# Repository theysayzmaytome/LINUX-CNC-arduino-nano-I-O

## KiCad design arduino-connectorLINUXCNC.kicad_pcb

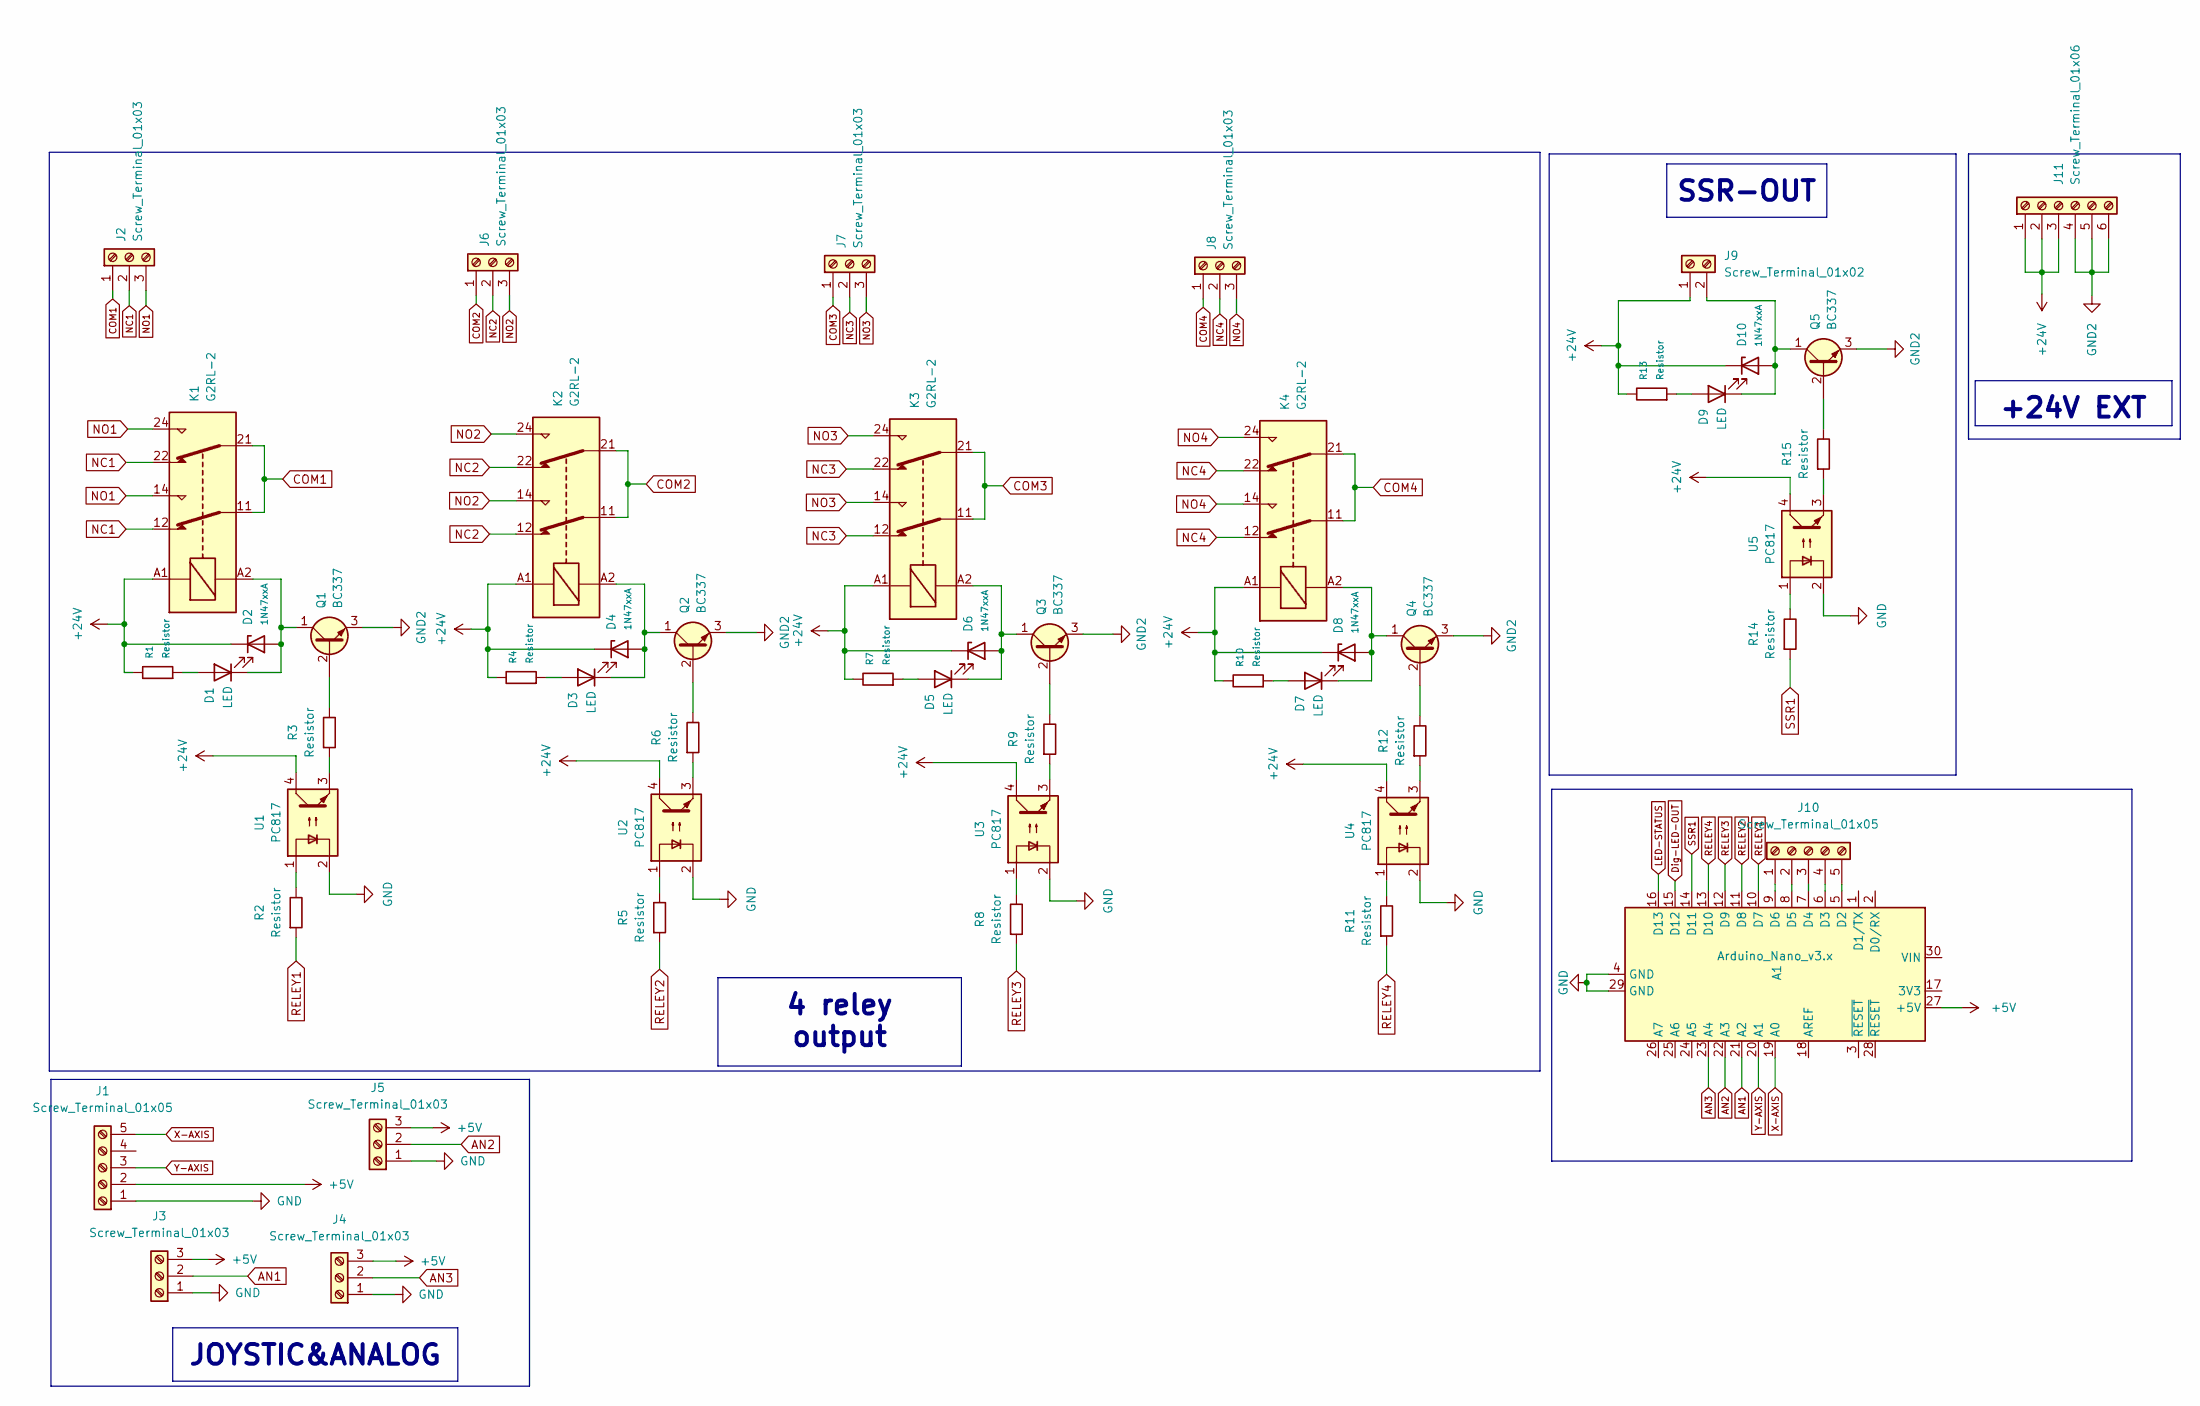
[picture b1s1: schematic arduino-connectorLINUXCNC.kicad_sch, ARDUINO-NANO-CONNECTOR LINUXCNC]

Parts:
A1: Arduino_Nano_v3.x; Arduino_Nano
D1, D3, D5, D7, D9: LED; LED_D5.0mm
D2, D4, D6, D8, D10: 1N47xxA; D_DO-41_SOD81_P10.16mm_Horizontal
J1, J10: Screw_Terminal_01x05; TerminalBlock_MetzConnect_Type011_RT05505HBWC_1x05_P5.00mm_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
J2, J3, J4, J5, J6, J7, J8: Screw_Terminal_01x03; TerminalBlock_Phoenix_MKDS-1,5-3_1x03_P5.00mm_Horizontal
J9: Screw_Terminal_01x02; TerminalBlock_Phoenix_MKDS-1,5-2-5.08_1x02_P5.08mm_Horizont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
J11: Screw_Terminal_01x06; TerminalBlock_Phoenix_MKDS-1,5-6_1x06_P5.00mm_Horizontal
K1, K2, K3, K4: G2RL-2; Relay_DPDT_Omron_G2RL-2
Q1, Q2, Q3, Q4, Q5: BC337; TO-92
R1, R2, R3, R4, R5, R6, R7, R8, R9, R10, R11, R12, R13, R14, R15: Resistor; R_Axial_DIN0207_L6.3mm_D2.5mm_P10.16mm_Horizontal
U1, U2, U3, U4, U5: PC817; DIP-4_W7.62mm

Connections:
+5V: A1.27 (+5V), J1.2, J3.3, J4.3, J5.3
+24V: D2.1 (K), D4.1 (K), D6.1 (K), D8.1 (K), D10.1 (K), J9.1, J11.1, J11.2, J11.3, K1.A1, K2.A1, K3.A1, K4.A1, R1.2, R4.2, R7.2, R10.2, R13.2, U1.4, U2.4, U3.4, U4.4, U5.4
AN1: A1.21 (A2), J3.2
AN2: A1.22 (A3), J5.2
AN3: A1.23 (A4), J4.2
COM1: J2.1, K1.11, K1.21
COM2: J6.1, K2.11, K2.21
COM3: J7.1, K3.11, K3.21
COM4: J8.1, K4.11, K4.21
Dig-LED-OUT: A1.15 (D12)
GND: A1.4 (GND), A1.29 (GND), J1.1, J3.1, J4.1, J5.1, U1.2, U2.2, U3.2, U4.2, U5.2
GND2: J11.4, J11.5, J11.6, Q1.3 (E), Q2.3 (E), Q3.3 (E), Q4.3 (E), Q5.3 (E)
LED-STATUS: A1.16 (D13)
NC1: J2.2, K1.12, K1.22
NC2: J6.2, K2.12, K2.22
NC3: J7.2, K3.12, K3.22
NC4: J8.2, K4.12, K4.22
NO1: J2.3, K1.14, K1.24
NO2: J6.3, K2.14, K2.24
NO3: J7.3, K3.14, K3.24
NO4: J8.3, K4.14, K4.24
unnamed: A1.5 (D2), J10.5
unnamed: A1.6 (D3), J10.4
unnamed: A1.7 (D4), J10.3
unnamed: A1.8 (D5), J10.2
unnamed: A1.9 (D6), J10.1
unnamed: D1.2 (A), R1.1
unnamed: D1.1 (K), D2.2 (A), K1.A2, Q1.1 (C)
unnamed: D3.2 (A), R4.1
unnamed: D3.1 (K), D4.2 (A), K2.A2, Q2.1 (C)
unnamed: D5.2 (A), R7.1
unnamed: D5.1 (K), D6.2 (A), K3.A2, Q3.1 (C)
unnamed: D7.2 (A), R10.1
unnamed: D7.1 (K), D8.2 (A), K4.A2, Q4.1 (C)
unnamed: D9.2 (A), R13.1
unnamed: D9.1 (K), D10.2 (A), J9.2, Q5.1 (C)
unnamed: Q1.2 (B), R3.2
unnamed: Q2.2 (B), R6.2
unnamed: Q3.2 (B), R9.2
unnamed: Q4.2 (B), R12.2
unnamed: Q5.2 (B), R15.2
unnamed: R2.2, U1.1
unnamed: R3.1, U1.3
unnamed: R5.2, U2.1
unnamed: R6.1, U2.3
unnamed: R8.2, U3.1
unnamed: R9.1, U3.3
unnamed: R11.2, U4.1
unnamed: R12.1, U4.3
unnamed: R14.2, U5.1
unnamed: R15.1, U5.3
RELEY1: A1.10 (D7), R2.1
RELEY2: A1.11 (D8), R5.1
RELEY3: A1.12 (D9), R8.1
RELEY4: A1.13 (D10), R11.1
SSR1: A1.14 (D11), R14.1
X-AXIS: A1.19 (A0), J1.5
Y-AXIS: A1.20 (A1), J1.3

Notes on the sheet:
4 reley output
+24V EXT
JOYSTIC&ANALOG
SSR-OUT

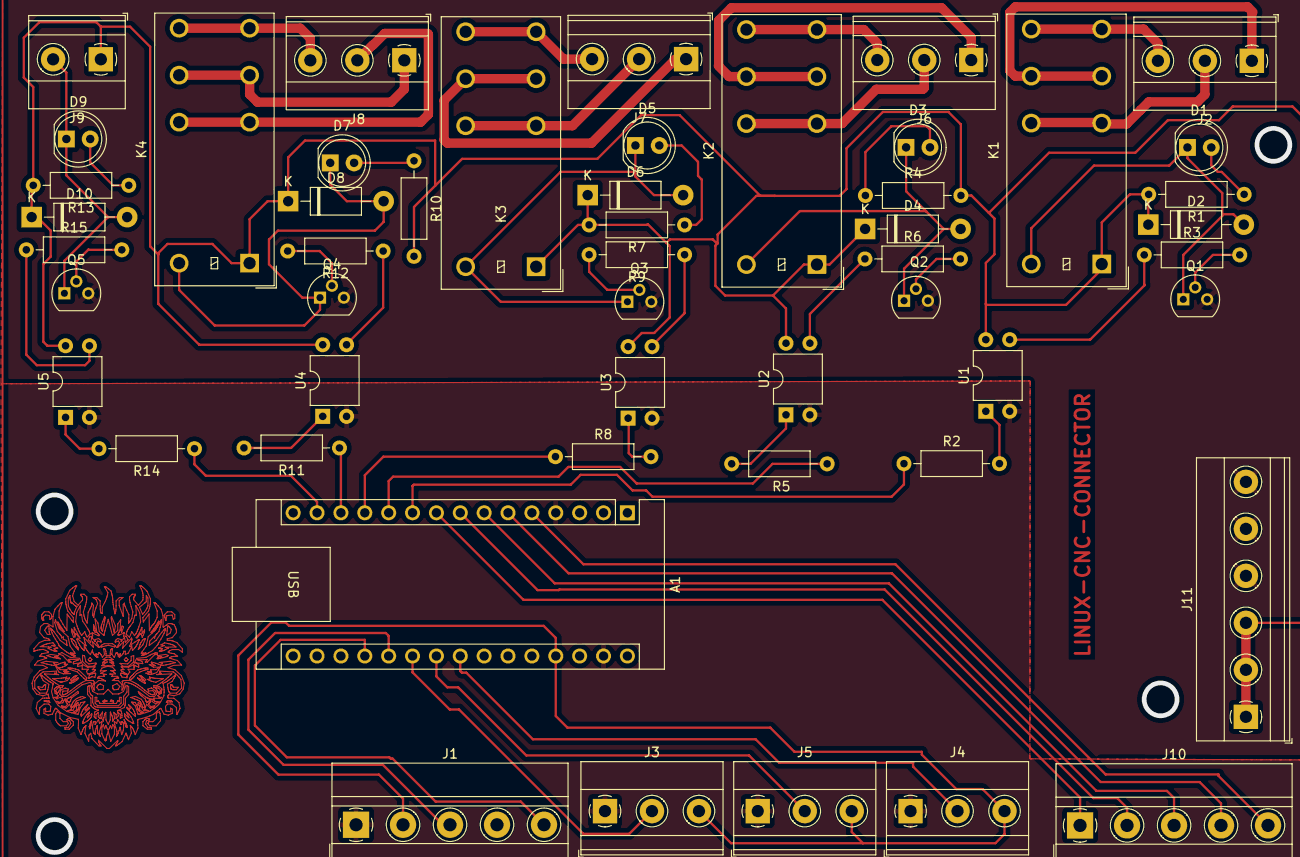
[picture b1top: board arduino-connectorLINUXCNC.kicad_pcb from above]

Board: 2 copper layers, 51 parts (0 on the bottom side), 56 nets.
